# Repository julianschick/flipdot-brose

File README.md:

# flipdot-brose
Leiterplattenlayout für die Ansteuerung von Brose-Flipdotmodulen.

## Teileliste

Mit passenden Artikelbezeichnungen für den Berliner Elektroteilehändler [Segor](https://www.segor.de).

Anzahl | Beschreibung | Segor-Artikelbezeichnung
--|--|--
2 | Hohlsteckerbuchse für Printmontage 2,1/5,5mm | *DCBU 2,1-PRNB*
3 | Miniatursicherungshalter Littelfuse RM 5,08mm | *RSI-Halter/LP*
3 | Rundsicherungen träge (1A, 4A, 5A) | *RSI 1,0 A T*; *RSI 4,0 A T*; *RSI 5,0 A T*
1 | JST VH-Buchse 3-polig 90° | *B3PS-VH*
1 | Diode mind. 2A und 30V | *1N 5062*
1 | Diode mind. 6A und 5V | *P 600 M*
1 | Keramikkondensator 100n RM 2,5mm | *u10-R2.5-X7R*
1 | Elektrolytkondensator 10u RM 2,5mm | *ELRA 10u-50/105°/6,3x7*
1 | Linearregler 3.3V min. 500mA Formfaktor TO220 | *LD 1117 V33* 
6 | Shift-Register 8Bit 74HC595 | *74HC 595 N*
1 | Octal-Transceiver 76HC245 | *74HC 245 N*
4 | NPN-Darlington-Array 8 Bit ULN2803A | *ULN 2803 A*
2 | High-Side-Driver TD62783 (oder UDN2981) | *TD62783 APG*
8 | Widerstand 10K RM 5,08mm |
1 | ESP32-Development-Board NodeMCU/DEVKITV1 (15 Pole je Reihe und VCC- und GND-Pin nebeneinander)
1 | Wannenstecker 60-polig (2x30) RM 2,54mm mit (oder ohne) Niederhalter
1 | Pinheader 10-polig (2x5) RM 2,54mm (und passende Kurzschlussbrücken dazu)
2 | Pinheader 16-polig RM 2,54mm (eigentlich 15-polig)

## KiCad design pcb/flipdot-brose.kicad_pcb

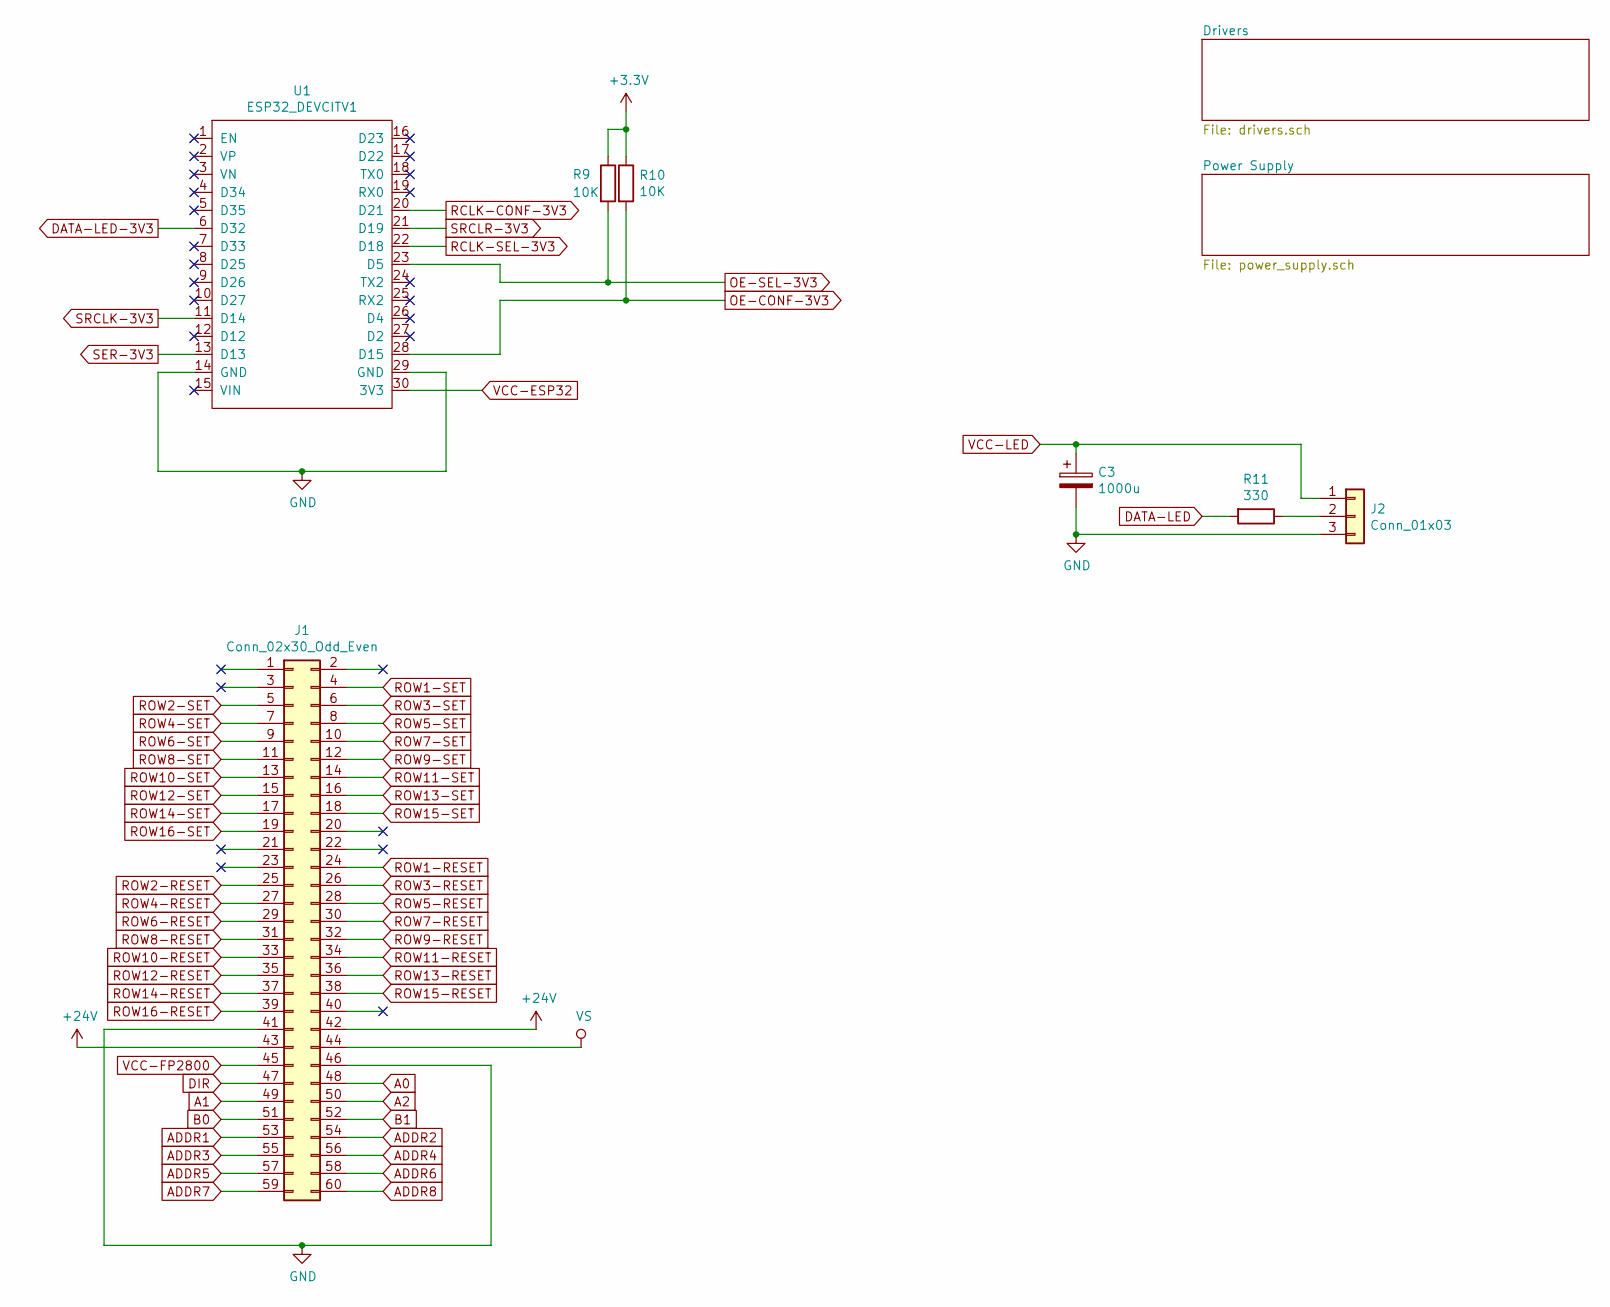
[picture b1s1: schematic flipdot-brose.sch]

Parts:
C3: 1000u; CP_Radial_D10.0mm_P5.00mm
J1: Conn_02x30_Odd_Even; IDC-Header_2x30_P2.54mm_Vertical_Lock
J2: Conn_01x03; JST_VH_B3PS-VH_2x3x3.96mm_Horizontal
R9, R10: 10K; R_Axial_DIN0204_L3.6mm_D1.6mm_P5.08mm_Horizontal
R11: 330; R_Axial_DIN0204_L3.6mm_D1.6mm_P5.08mm_Horizontal
U1: ESP32_DEVCITV1; ESP32_DEVKITV1

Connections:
+3V3: R9.1, R10.1; also elsewhere on the board
+24V: J1.42, J1.43; also elsewhere on the board
A0: J1.48; also elsewhere on the board
A1: J1.49; also elsewhere on the board
A2: J1.50; also elsewhere on the board
ADDR1: J1.53; also elsewhere on the board
ADDR2: J1.54; also elsewhere on the board
ADDR3: J1.55; also elsewhere on the board
ADDR4: J1.56; also elsewhere on the board
ADDR5: J1.57; also elsewhere on the board
ADDR6: J1.58; also elsewhere on the board
ADDR7: J1.59; also elsewhere on the board
ADDR8: J1.60; also elsewhere on the board
B0: J1.51; also elsewhere on the board
B1: J1.52; also elsewhere on the board
DATA-LED: R11.2; also elsewhere on the board
DATA-LED-3V3: U1.6 (D32); also elsewhere on the board
DIR: J1.47; also elsewhere on the board
GND: C3.2, J1.41, J1.46, J2.3, U1.14 (GND), U1.29 (GND); also elsewhere on the board
unnamed: J2.2, R11.1
OE-CONF-3V3: R10.2, U1.28 (D15); also elsewhere on the board
OE-SEL-3V3: R9.2, U1.23 (D5); also elsewhere on the board
RCLK-CONF-3V3: U1.20 (D21); also elsewhere on the board
RCLK-SEL-3V3: U1.22 (D18); also elsewhere on the board
ROW1-RESET: J1.24; also elsewhere on the board
ROW1-SET: J1.4; also elsewhere on the board
ROW2-RESET: J1.25; also elsewhere on the board
ROW2-SET: J1.5; also elsewhere on the board
ROW3-RESET: J1.26; also elsewhere on the board
ROW3-SET: J1.6; also elsewhere on the board
ROW4-RESET: J1.27; also elsewhere on the board
ROW4-SET: J1.7; also elsewhere on the board
ROW5-RESET: J1.28; also elsewhere on the board
ROW5-SET: J1.8; also elsewhere on the board
ROW6-RESET: J1.29; also elsewhere on the board
ROW6-SET: J1.9; also elsewhere on the board
ROW7-RESET: J1.30; also elsewhere on the board
ROW7-SET: J1.10; also elsewhere on the board
ROW8-RESET: J1.31; also elsewhere on the board
ROW8-SET: J1.11; also elsewhere on the board
ROW9-RESET: J1.32; also elsewhere on the board
ROW9-SET: J1.12; also elsewhere on the board
ROW10-RESET: J1.33; also elsewhere on the board
ROW10-SET: J1.13; also elsewhere on the board
ROW11-RESET: J1.34; also elsewhere on the board
ROW11-SET: J1.14; also elsewhere on the board
ROW12-RESET: J1.35; also elsewhere on the board
ROW12-SET: J1.15; also elsewhere on the board
ROW13-RESET: J1.36; also elsewhere on the board
ROW13-SET: J1.16; also elsewhere on the board
ROW14-RESET: J1.37; also elsewhere on the board
ROW14-SET: J1.17; also elsewhere on the board
ROW15-RESET: J1.38; also elsewhere on the board
ROW15-SET: J1.18; also elsewhere on the board
ROW16-RESET: J1.39; also elsewhere on the board
ROW16-SET: J1.19; also elsewhere on the board
SER-3V3: U1.13 (D13); also elsewhere on the board
SRCLK-3V3: U1.11 (D14); also elsewhere on the board
SRCLR-3V3: U1.21 (D19); also elsewhere on the board
VCC-ESP32: U1.30 (3V3); also elsewhere on the board
VCC-FP2800: J1.45; also elsewhere on the board
VCC-LED: C3.1, J2.1; also elsewhere on the board
VS: J1.44; also elsewhere on the board

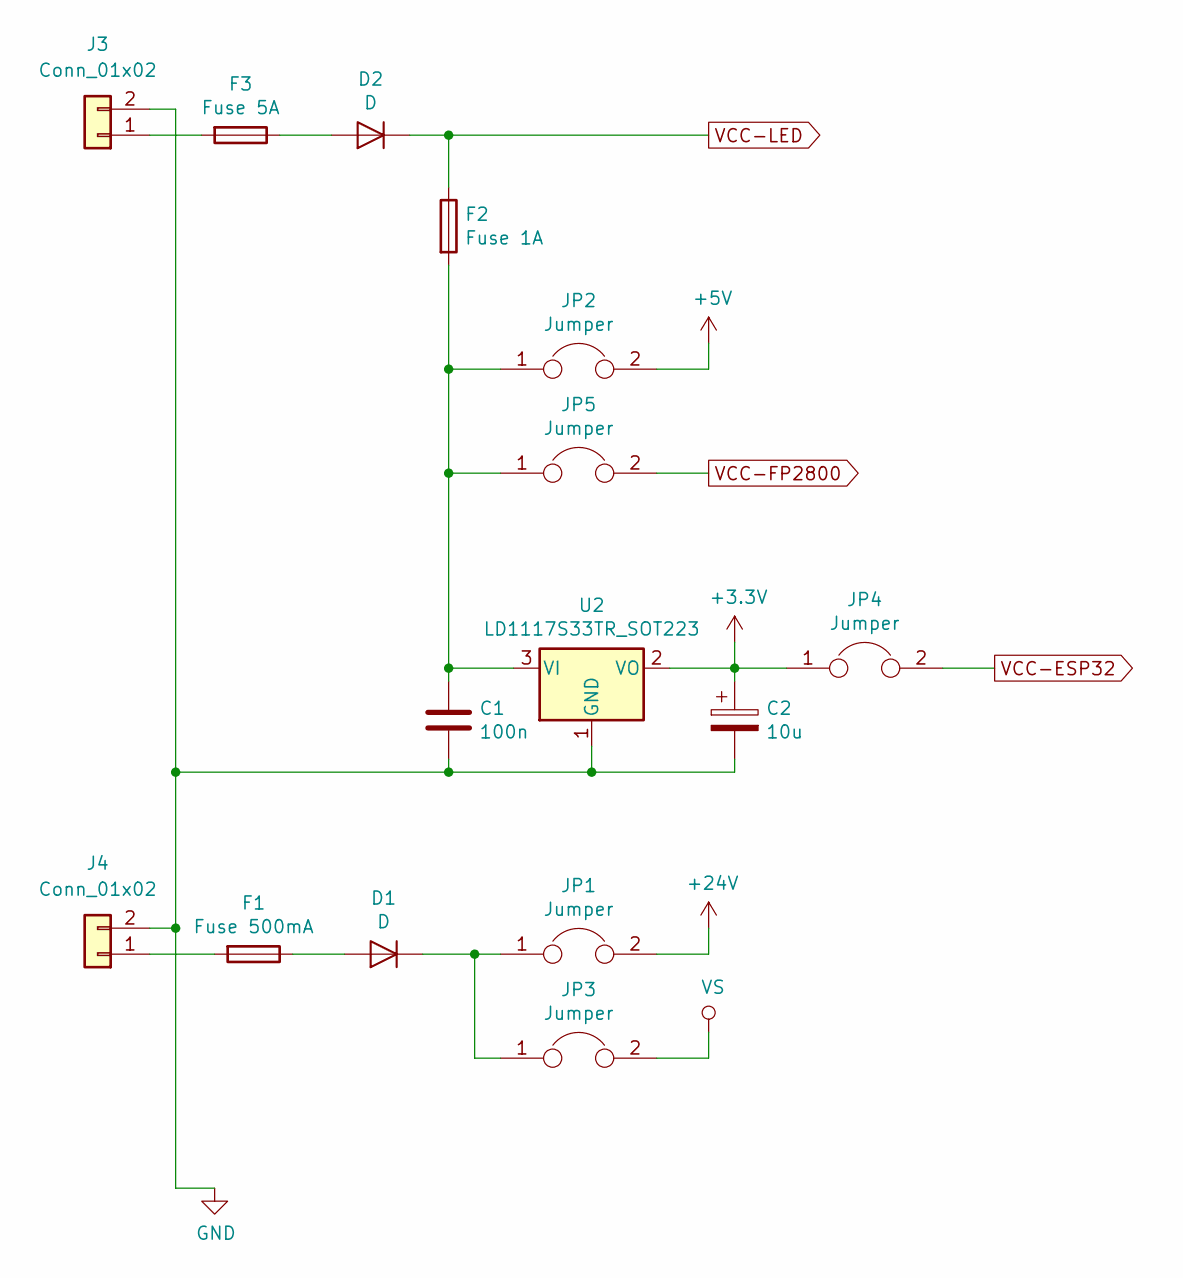
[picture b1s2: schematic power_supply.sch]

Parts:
C1: 100n; C_Disc_D5.0mm_W2.5mm_P2.50mm
C2: 10u; CP_Radial_D5.0mm_P2.50mm
D1: D; D_A-405_P7.62mm_Horizontal
D2: D; D_P600_R-6_P12.70mm_Horizontal
F1: Fuse 500mA; Fuseholder_Fuse_TR5_Littlefuse-No560_No460
F2: Fuse 1A; Fuseholder_Fuse_TR5_Littlefuse-No560_No460
F3: Fuse 5A; Fuseholder_Fuse_TR5_Littlefuse-No560_No460
J3, J4: Conn_01x02; TerminalBlock_MetzConnect_Type055_RT01502HDWU_Pitch5.00mm
JP1, JP2, JP3, JP4, JP5: Jumper; PinHeader_1x02_P2.54mm_Vertical
U2: LD1117S33TR_SOT223; TO-220-3_Horizontal

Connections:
+3V3: C2.1, JP4.1, U2.2 (VO); also elsewhere on the board
+5V: JP2.2; also elsewhere on the board
+24V: JP1.2; also elsewhere on the board
GND: C1.2, C2.2, J3.2, J4.2, U2.1 (GND); also elsewhere on the board
unnamed: C1.1, F2.2, JP2.1, JP5.1, U2.3 (VI)
unnamed: D1.1 (K), JP1.1, JP3.1
unnamed: D1.2 (A), F1.1
unnamed: D2.2 (A), F3.1
unnamed: F1.2, J4.1
unnamed: F3.2, J3.1
VCC-ESP32: JP4.2; also elsewhere on the board
VCC-FP2800: JP5.2; also elsewhere on the board
VCC-LED: D2.1 (K), F2.1; also elsewhere on the board
VS: JP3.2; also elsewhere on the board

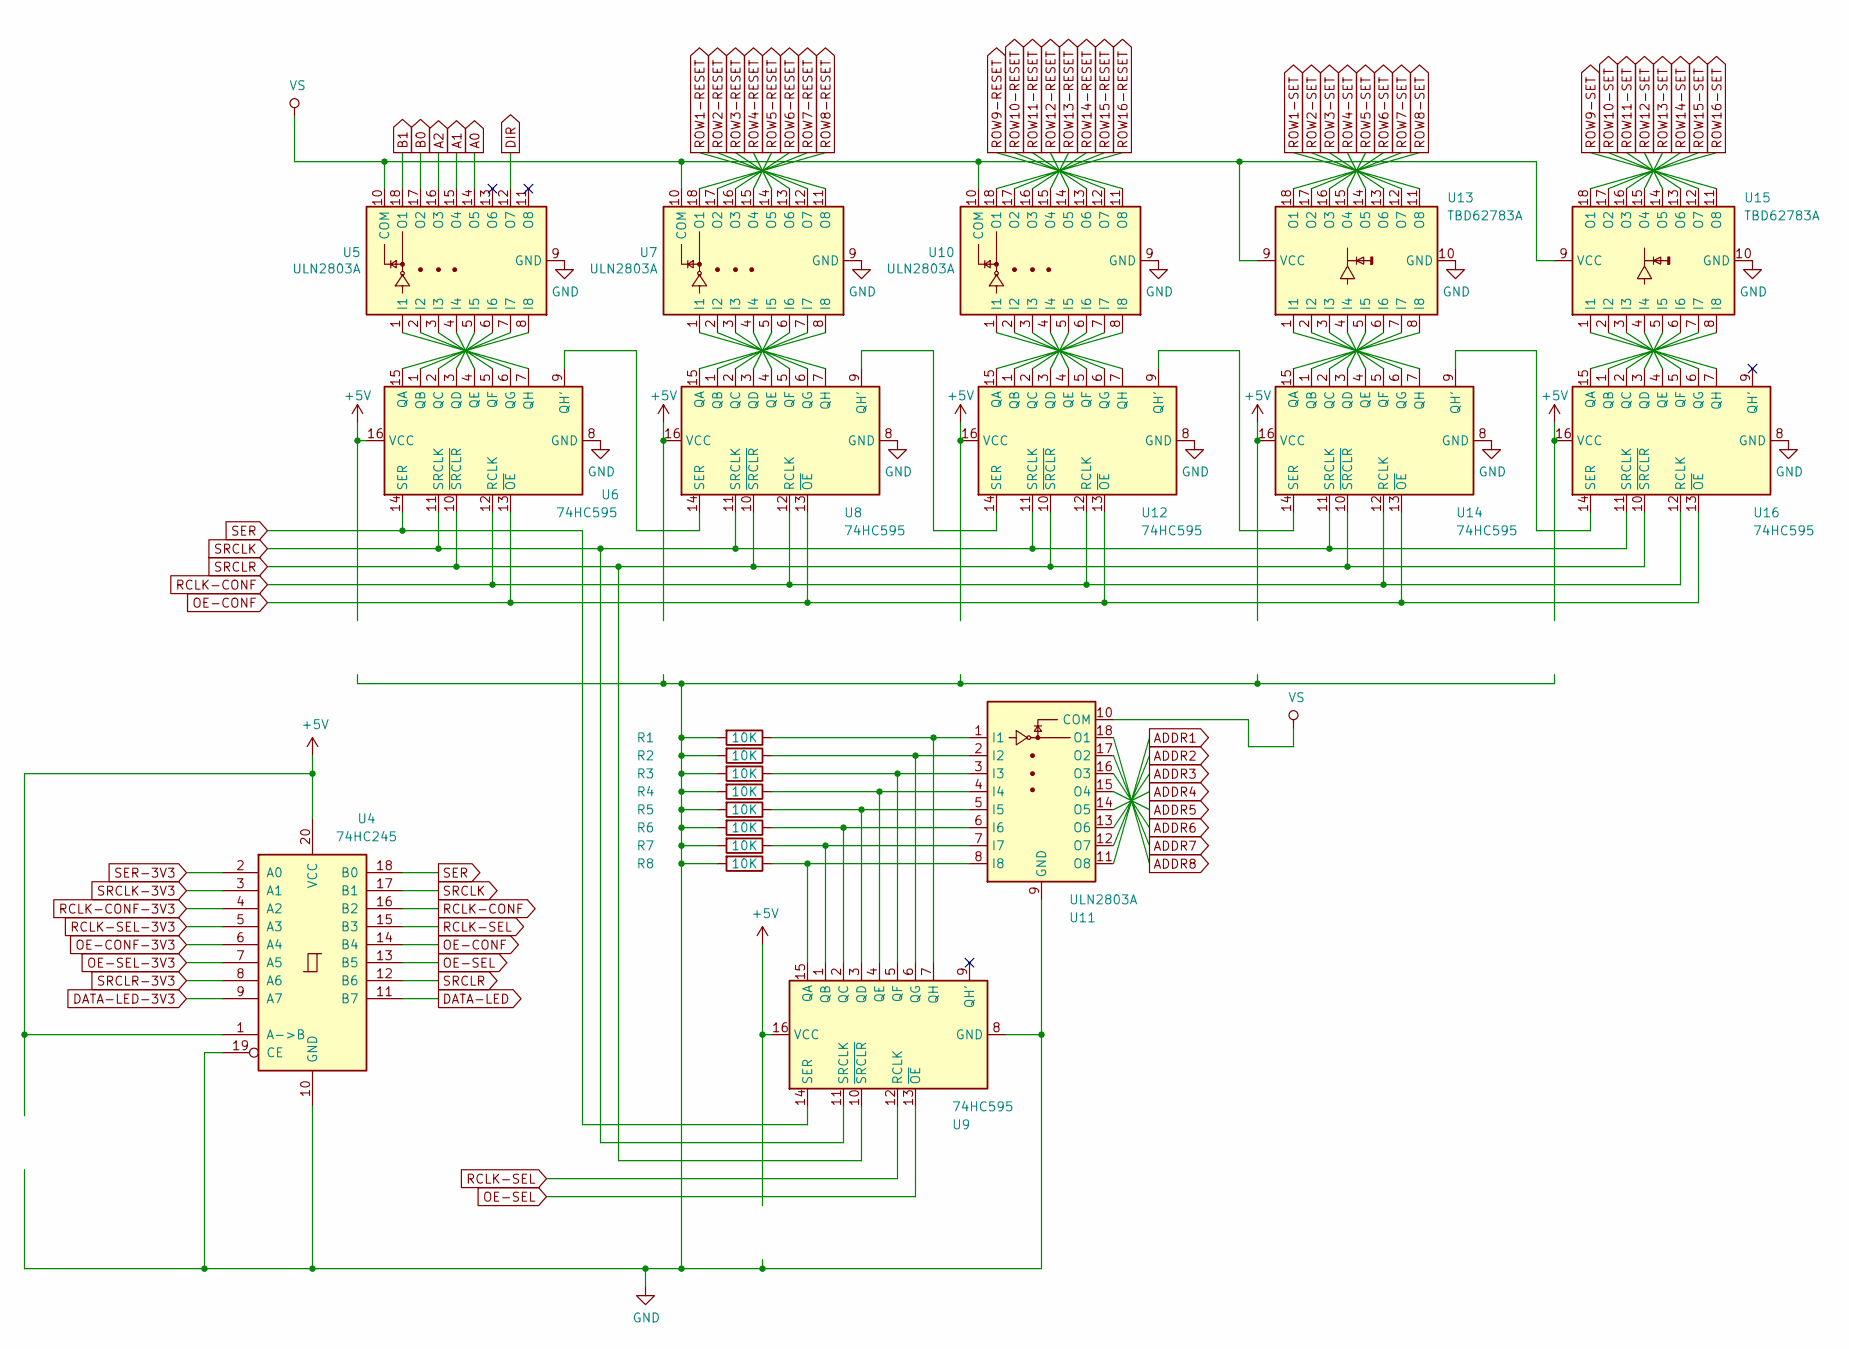
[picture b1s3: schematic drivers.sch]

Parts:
R1, R2, R3, R4, R5, R6, R7, R8: 10K; R_Axial_DIN0204_L3.6mm_D1.6mm_P5.08mm_Horizontal
U4: 74HC245; DIP-20_W7.62mm
U5, U7, U10, U11: ULN2803A; DIP-18_W7.62mm
U6, U8, U9, U12, U14, U16: 74HC595; DIP-16_W7.62mm
U13, U15: TBD62783A; DIP-18_W7.62mm

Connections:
+5V: U4.1 (A->B), U4.20 (VCC), U6.16 (VCC), U8.16 (VCC), U9.16 (VCC), U12.16 (VCC), U14.16 (VCC), U16.16 (VCC); also elsewhere on the board
A0: U5.14 (O5); also elsewhere on the board
A1: U5.15 (O4); also elsewhere on the board
A2: U5.16 (O3); also elsewhere on the board
ADDR1: U11.11 (O8); also elsewhere on the board
ADDR2: U11.12 (O7); also elsewhere on the board
ADDR3: U11.13 (O6); also elsewhere on the board
ADDR4: U11.14 (O5); also elsewhere on the board
ADDR5: U11.15 (O4); also elsewhere on the board
ADDR6: U11.16 (O3); also elsewhere on the board
ADDR7: U11.17 (O2); also elsewhere on the board
ADDR8: U11.18 (O1); also elsewhere on the board
B0: U5.17 (O2); also elsewhere on the board
B1: U5.18 (O1); also elsewhere on the board
DATA-LED: U4.11 (B7); also elsewhere on the board
DATA-LED-3V3: U4.9 (A7); also elsewhere on the board
DIR: U5.12 (O7); also elsewhere on the board
GND: R1.2, R2.2, R3.2, R4.2, R5.2, R6.2, R7.2, R8.2, U4.10 (GND), U4.19 (CE), U5.9 (GND), U6.8 (GND), U7.9 (GND), U8.8 (GND), U9.8 (GND), U10.9 (GND), U11.9 (GND), U12.8 (GND), U13.10 (GND), U14.8 (GND), U15.10 (GND), U16.8 (GND); also elsewhere on the board
unnamed: R1.1, U9.7 (QH), U11.1 (I1)
unnamed: R2.1, U9.6 (QG), U11.2 (I2)
unnamed: R3.1, U9.5 (QF), U11.3 (I3)
unnamed: R4.1, U9.4 (QE), U11.4 (I4)
unnamed: R5.1, U9.3 (QD), U11.5 (I5)
unnamed: R6.1, U9.2 (QC), U11.6 (I6)
unnamed: R7.1, U9.1 (QB), U11.7 (I7)
unnamed: R8.1, U9.15 (QA), U11.8 (I8)
unnamed: U5.1 (I1), U6.7 (QH)
unnamed: U5.2 (I2), U6.6 (QG)
unnamed: U5.3 (I3), U6.5 (QF)
unnamed: U5.4 (I4), U6.4 (QE)
unnamed: U5.5 (I5), U6.3 (QD)
unnamed: U5.6 (I6), U6.2 (QC)
unnamed: U5.7 (I7), U6.1 (QB)
unnamed: U5.8 (I8), U6.15 (QA)
unnamed: U6.9 (QH'), U8.14 (SER)
unnamed: U7.1 (I1), U8.7 (QH)
unnamed: U7.2 (I2), U8.6 (QG)
unnamed: U7.3 (I3), U8.5 (QF)
unnamed: U7.4 (I4), U8.4 (QE)
unnamed: U7.5 (I5), U8.3 (QD)
unnamed: U7.6 (I6), U8.2 (QC)
unnamed: U7.7 (I7), U8.1 (QB)
unnamed: U7.8 (I8), U8.15 (QA)
unnamed: U10.1 (I1), U12.7 (QH)
unnamed: U10.2 (I2), U12.6 (QG)
unnamed: U10.3 (I3), U12.5 (QF)
unnamed: U10.4 (I4), U12.4 (QE)
unnamed: U10.5 (I5), U12.3 (QD)
unnamed: U10.6 (I6), U12.2 (QC)
unnamed: U10.7 (I7), U12.1 (QB)
unnamed: U10.8 (I8), U12.15 (QA)
unnamed: U12.9 (QH'), U14.14 (SER)
unnamed: U8.9 (QH'), U12.14 (SER)
unnamed: U13.1 (I1), U14.7 (QH)
unnamed: U13.2 (I2), U14.6 (QG)
unnamed: U13.3 (I3), U14.5 (QF)
unnamed: U13.4 (I4), U14.4 (QE)
unnamed: U13.5 (I5), U14.3 (QD)
unnamed: U13.6 (I6), U14.2 (QC)
unnamed: U13.7 (I7), U14.1 (QB)
unnamed: U13.8 (I8), U14.15 (QA)
unnamed: U14.9 (QH'), U16.14 (SER)
unnamed: U15.1 (I1), U16.7 (QH)
unnamed: U15.2 (I2), U16.6 (QG)
unnamed: U15.3 (I3), U16.5 (QF)
unnamed: U15.4 (I4), U16.4 (QE)
unnamed: U15.5 (I5), U16.3 (QD)
unnamed: U15.6 (I6), U16.2 (QC)
unnamed: U15.7 (I7), U16.1 (QB)
unnamed: U15.8 (I8), U16.15 (QA)
OE-CONF: U4.14 (B4), U6.13 (~OE), U8.13 (~OE), U12.13 (~OE), U14.13 (~OE), U16.13 (~OE)
OE-CONF-3V3: U4.6 (A4); also elsewhere on the board
OE-SEL: U4.13 (B5), U9.13 (~OE)
OE-SEL-3V3: U4.7 (A5); also elsewhere on the board
RCLK-CONF: U4.16 (B2), U6.12 (RCLK), U8.12 (RCLK), U12.12 (RCLK), U14.12 (RCLK), U16.12 (RCLK)
RCLK-CONF-3V3: U4.4 (A2); also elsewhere on the board
RCLK-SEL: U4.15 (B3), U9.12 (RCLK)
RCLK-SEL-3V3: U4.5 (A3); also elsewhere on the board
ROW1-RESET: U7.11 (O8); also elsewhere on the board
ROW1-SET: U13.11 (O8); also elsewhere on the board
ROW2-RESET: U7.12 (O7); also elsewhere on the board
ROW2-SET: U13.12 (O7); also elsewhere on the board
ROW3-RESET: U7.13 (O6); also elsewhere on the board
ROW3-SET: U13.13 (O6); also elsewhere on the board
ROW4-RESET: U7.14 (O5); also elsewhere on the board
ROW4-SET: U13.14 (O5); also elsewhere on the board
ROW5-RESET: U7.15 (O4); also elsewhere on the board
ROW5-SET: U13.15 (O4); also elsewhere on the board
ROW6-RESET: U7.16 (O3); also elsewhere on the board
ROW6-SET: U13.16 (O3); also elsewhere on the board
ROW7-RESET: U7.17 (O2); also elsewhere on the board
ROW7-SET: U13.17 (O2); also elsewhere on the board
ROW8-RESET: U7.18 (O1); also elsewhere on the board
ROW8-SET: U13.18 (O1); also elsewhere on the board
ROW9-RESET: U10.11 (O8); also elsewhere on the board
ROW9-SET: U15.11 (O8); also elsewhere on the board
ROW10-RESET: U10.12 (O7); also elsewhere on the board
ROW10-SET: U15.12 (O7); also elsewhere on the board
ROW11-RESET: U10.13 (O6); also elsewhere on the board
ROW11-SET: U15.13 (O6); also elsewhere on the board
ROW12-RESET: U10.14 (O5); also elsewhere on the board
ROW12-SET: U15.14 (O5); also elsewhere on the board
ROW13-RESET: U10.15 (O4); also elsewhere on the board
ROW13-SET: U15.15 (O4); also elsewhere on the board
ROW14-RESET: U10.16 (O3); also elsewhere on the board
ROW14-SET: U15.16 (O3); also elsewhere on the board
ROW15-RESET: U10.17 (O2); also elsewhere on the board
ROW15-SET: U15.17 (O2); also elsewhere on the board
ROW16-RESET: U10.18 (O1); also elsewhere on the board
ROW16-SET: U15.18 (O1); also elsewhere on the board
SER: U4.18 (B0), U6.14 (SER), U9.14 (SER)
SER-3V3: U4.2 (A0); also elsewhere on the board
SRCLK: U4.17 (B1), U6.11 (SRCLK), U8.11 (SRCLK), U9.11 (SRCLK), U12.11 (SRCLK), U14.11 (SRCLK), U16.11 (SRCLK)
SRCLK-3V3: U4.3 (A1); also elsewhere on the board
SRCLR: U4.12 (B6), U6.10 (~SRCLR), U8.10 (~SRCLR), U9.10 (~SRCLR), U12.10 (~SRCLR), U14.10 (~SRCLR), U16.10 (~SRCLR)
SRCLR-3V3: U4.8 (A6); also elsewhere on the board
VS: U5.10 (COM), U7.10 (COM), U10.10 (COM), U11.10 (COM), U13.9 (VCC), U15.9 (VCC); also elsewhere on the board

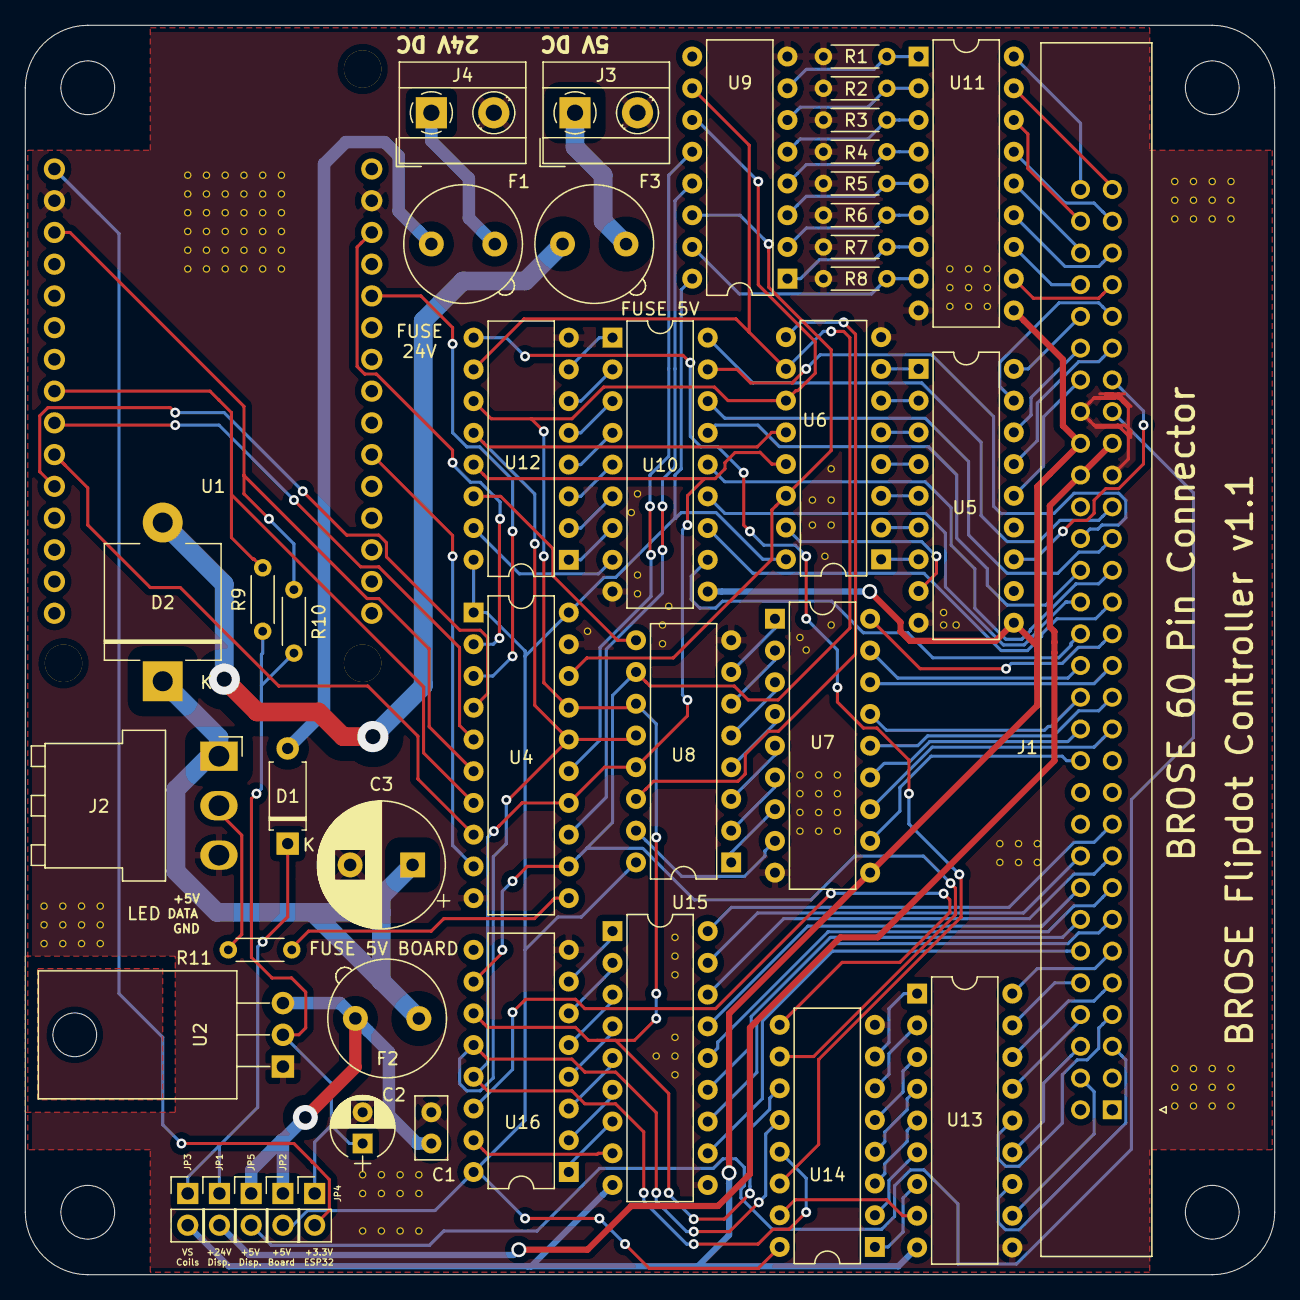
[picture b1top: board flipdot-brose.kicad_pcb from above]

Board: 2 copper layers, 100.0 x 100.0 mm, 43 parts (0 on the bottom side), 129 nets.

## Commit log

2019-12-14 first working c++ rev
2019-12-15 abstraction
2019-12-24 ws2812driver + partitions
2020-01-05 bitarray, led-driver, http-server
2020-01-19 pixelfonts / octafont / display-string
2020-01-28 pixelstring
2020-01-30 a bit of udp code
2020-02-12 tcp experiment
2020-02-12 pin change
2020-02-18 udp -> tcp
2020-02-26 pcb and firmware repo merge
2020-02-27 readme removed
2020-03-15 tcp server
2020-03-17 command interpreter
2020-03-17 submodule
2020-03-17 ringbuffer update
2020-03-21 show text and freq
2020-03-22 went back to idf v4.0
2020-03-26 tcp server hardened, wifi hostname
2020-03-27 font undercut
2020-03-27 resistor/capacitor for leds
2020-03-29 buffered led driver
2020-03-30 tcp log levels
2020-04-01 tcp protocol, transition modes
2020-04-02 task watching
2020-04-05 led slide, restructure
2020-04-08 ws2812buffer
2020-04-09 refactoring
2020-04-12 flipdot-task
2020-04-27 buffered flipdot
2020-04-27 flip2
2020-04-27 some getters and bugfixes
2020-05-08 flipui added
2020-05-08 bugfixes firmware
2020-05-16 flipui progress
2021-02-28 idf 4.2
2021-03-08 python pixel fonts
2021-03-09 api key removed
2021-03-10 text functions removed
2021-03-14 pixelfont utf and canvas
2021-03-14 bugfixes, qcommand
2021-04-17 firmware changes, new command
2021-04-17 new command 'Scroll'
2021-04-17 new command scroll
2021-04-17 sync with flapflask
2021-10-26 mysterious-changes
2024-11-16 opened with newer kicad-version
